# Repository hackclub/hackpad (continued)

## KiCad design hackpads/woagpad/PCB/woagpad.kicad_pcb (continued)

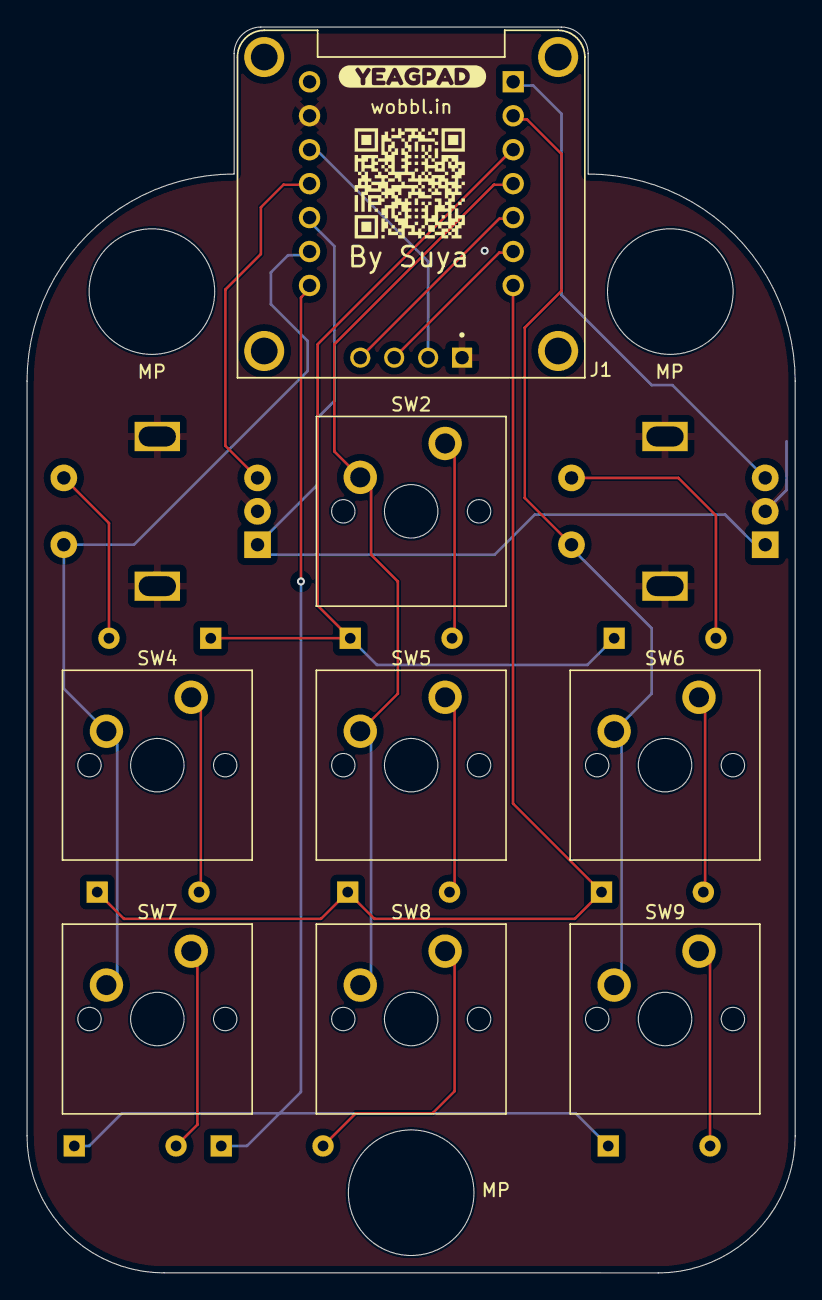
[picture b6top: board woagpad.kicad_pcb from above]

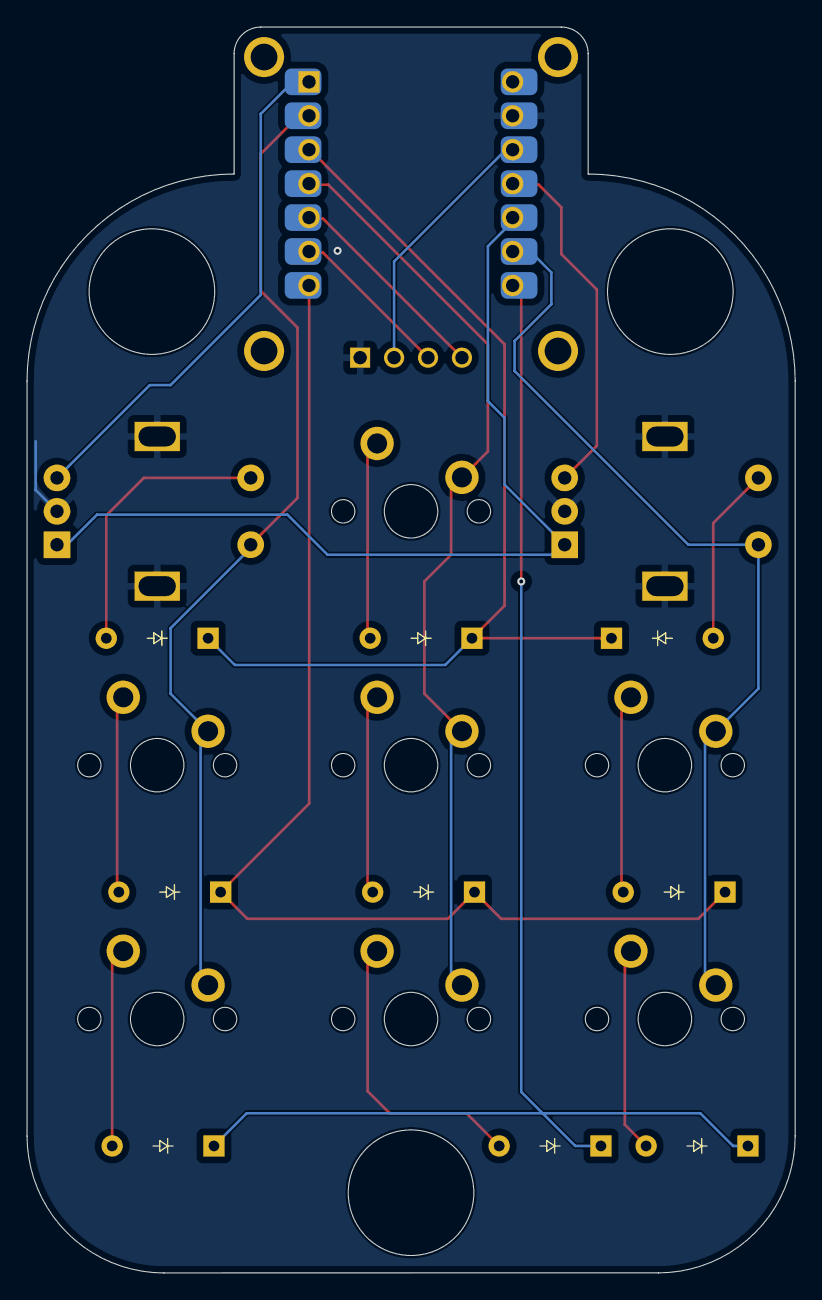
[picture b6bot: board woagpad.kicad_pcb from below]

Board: 2 copper layers, 57.5 x 93.2 mm, 22 parts (10 on the bottom side), 22 nets.

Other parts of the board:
QR*****: WobblQR
kibuzzard-67AA371A: G***; kibuzzard-67AA371A

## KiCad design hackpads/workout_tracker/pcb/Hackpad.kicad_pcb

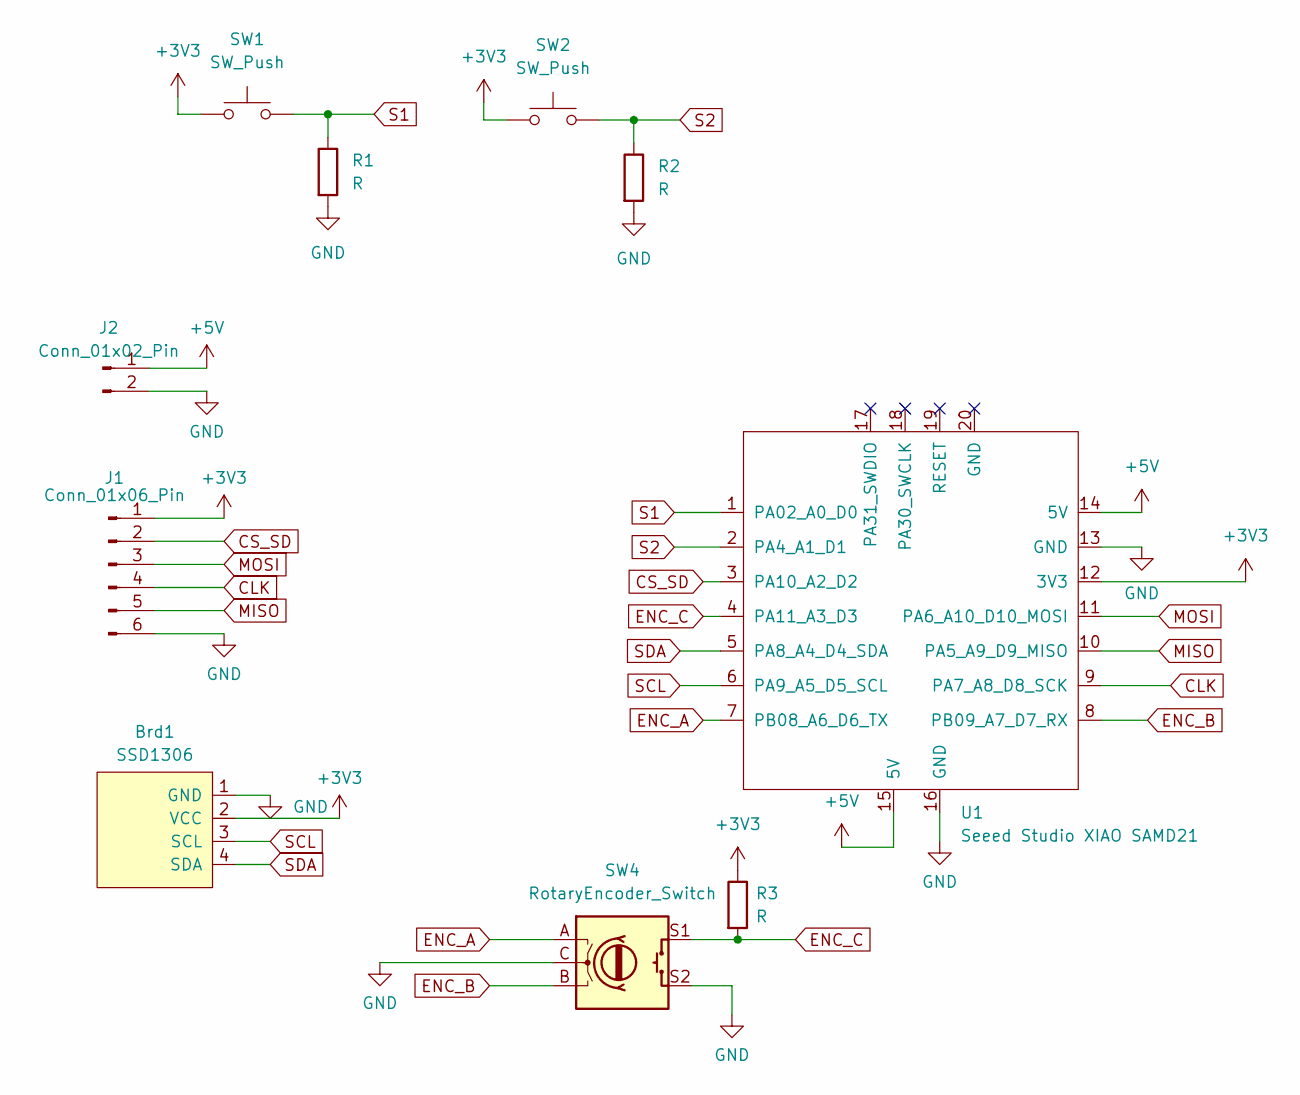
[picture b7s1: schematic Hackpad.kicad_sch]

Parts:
Brd1: SSD1306; SSD1306_128x64
J1: Conn_01x06_Pin; PinHeader_1x06_P2.54mm_Vertical
J2: Conn_01x02_Pin; PinHeader_1x02_P2.54mm_Vertical
R1, R2, R3: R; CF14JT4K70
SW1, SW2: SW_Push; SW_Cherry_MX_1.00u_PCB
SW4: RotaryEncoder_Switch; RotaryEncoder_Alps_EC11E-Switch_Vertical_H20mm
U1: Seeed Studio XIAO SAMD21; XIAO-SAMD21-RP2040-14P-2.54-21X17.8MM (Seeeduino XIAO)

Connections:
+3V3: Brd1.2 (VCC), J1.1, R3.1, SW1.1, SW2.1, U1.12 (3V3)
+5V: J2.1, U1.14 (5V), U1.15 (5V)
CLK: J1.4, U1.9 (PA7_A8_D8_SCK)
CS_SD: J1.2, U1.3 (PA10_A2_D2)
ENC_A: SW4.A, U1.7 (PB08_A6_D6_TX)
ENC_B: SW4.B, U1.8 (PB09_A7_D7_RX)
ENC_C: R3.2, SW4.S1, U1.4 (PA11_A3_D3)
GND: Brd1.1 (GND), J1.6, J2.2, R1.2, R2.2, SW4.C, SW4.S2, U1.13 (GND), U1.16 (GND)
MISO: J1.5, U1.10 (PA5_A9_D9_MISO)
MOSI: J1.3, U1.11 (PA6_A10_D10_MOSI)
S1: R1.1, SW1.2, U1.1 (PA02_A0_D0)
S2: R2.1, SW2.2, U1.2 (PA4_A1_D1)
SCL: Brd1.3 (SCL), U1.6 (PA9_A5_D5_SCL)
SDA: Brd1.4 (SDA), U1.5 (PA8_A4_D4_SDA)

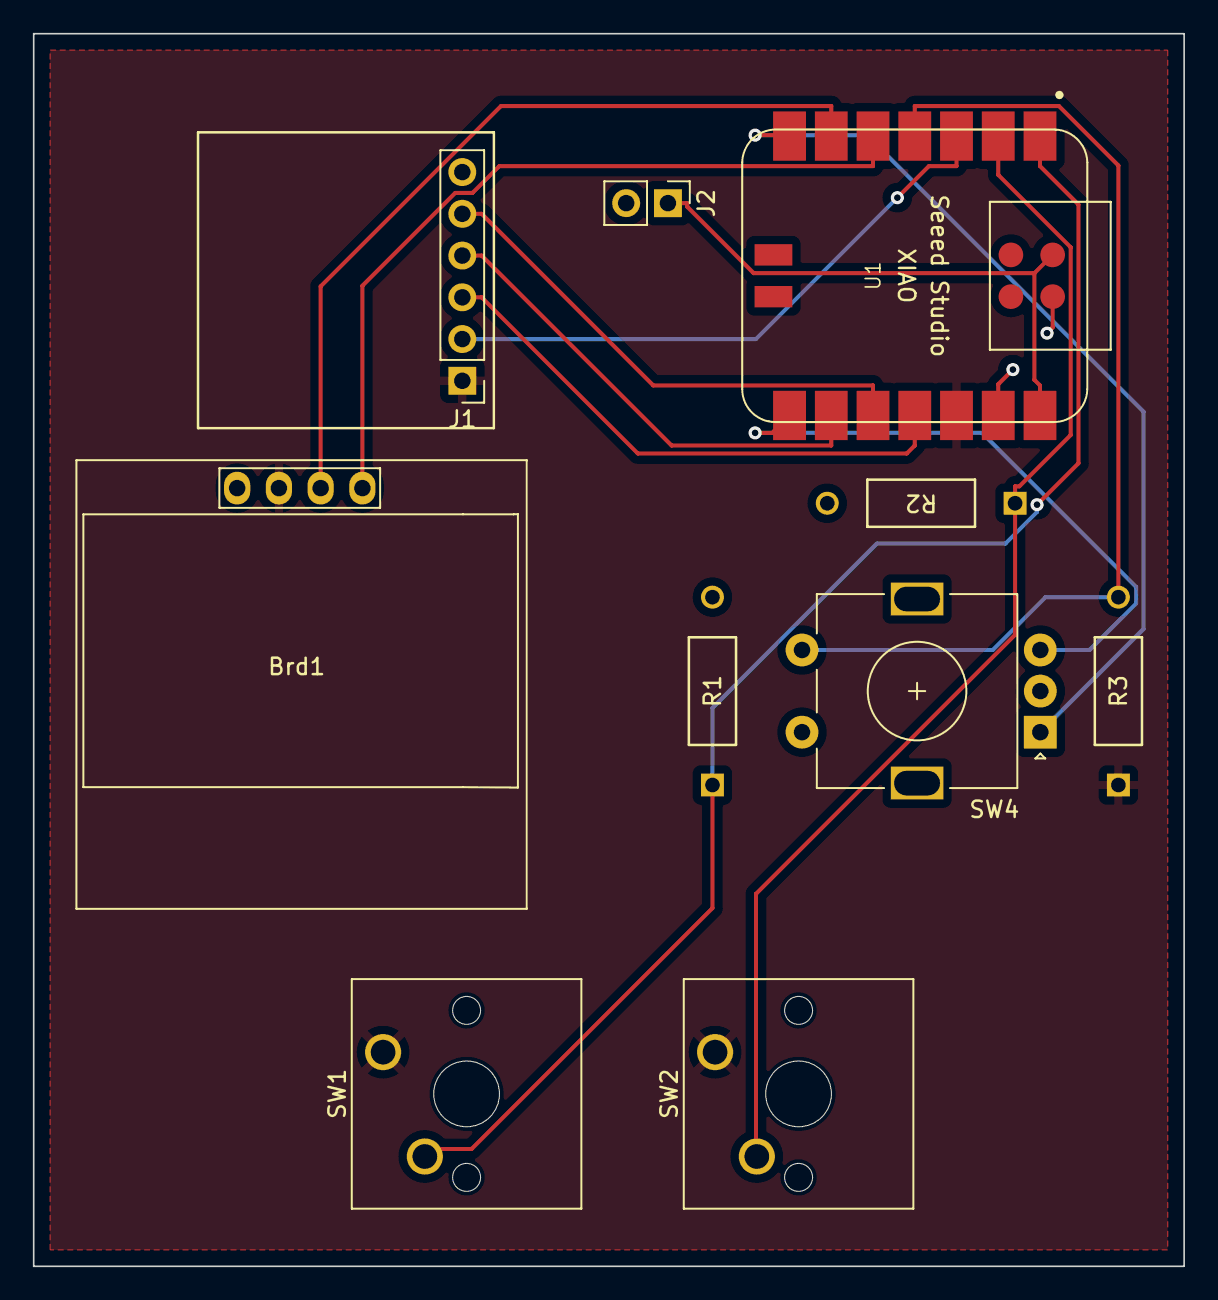
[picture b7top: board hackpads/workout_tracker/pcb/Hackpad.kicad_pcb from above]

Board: 2 copper layers, 70.0 x 75.0 mm, 10 parts (0 on the bottom side), 14 nets.
